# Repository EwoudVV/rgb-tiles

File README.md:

# RGB Tiles

modular 8 x 8 RGB LED tiles with an RP2040 on each board. connectors on all four edges let the tiles join into different shapes. all tiles face the same way

each tile is 99.5 mm square, with 64 WS2812C-V6 LEDs, 2 MB flash, USB-C and a four-layer PCB

open [rgb-tiles.kicad_pro](rgb-tiles.kicad_pro) in KiCad 10. [manufacturing/](manufacturing/) contains the Gerbers, drill files, BOM and purchase list. fabrication: four layers, 1.6 mm FR-4, JLC04161H-7628 stackup, 1 oz outer / 0.5 oz inner copper, lead-free HASL

power comes from a regulated 12 V supply at J7. USB is for data only. allow 1 A per tile and use a separate feed to each tile for full brightness. leave both edge power shunts out between separately fed sections. support the boards with a frame

[test firmware](firmware/README.md) displays dim red, green and blue stripes and reports received neighbor markers over USB serial

[Hack Club Half Life, week 4](https://halflife.hackclub.com/projects/c01og00redvbnb7qoo1i9yo8)

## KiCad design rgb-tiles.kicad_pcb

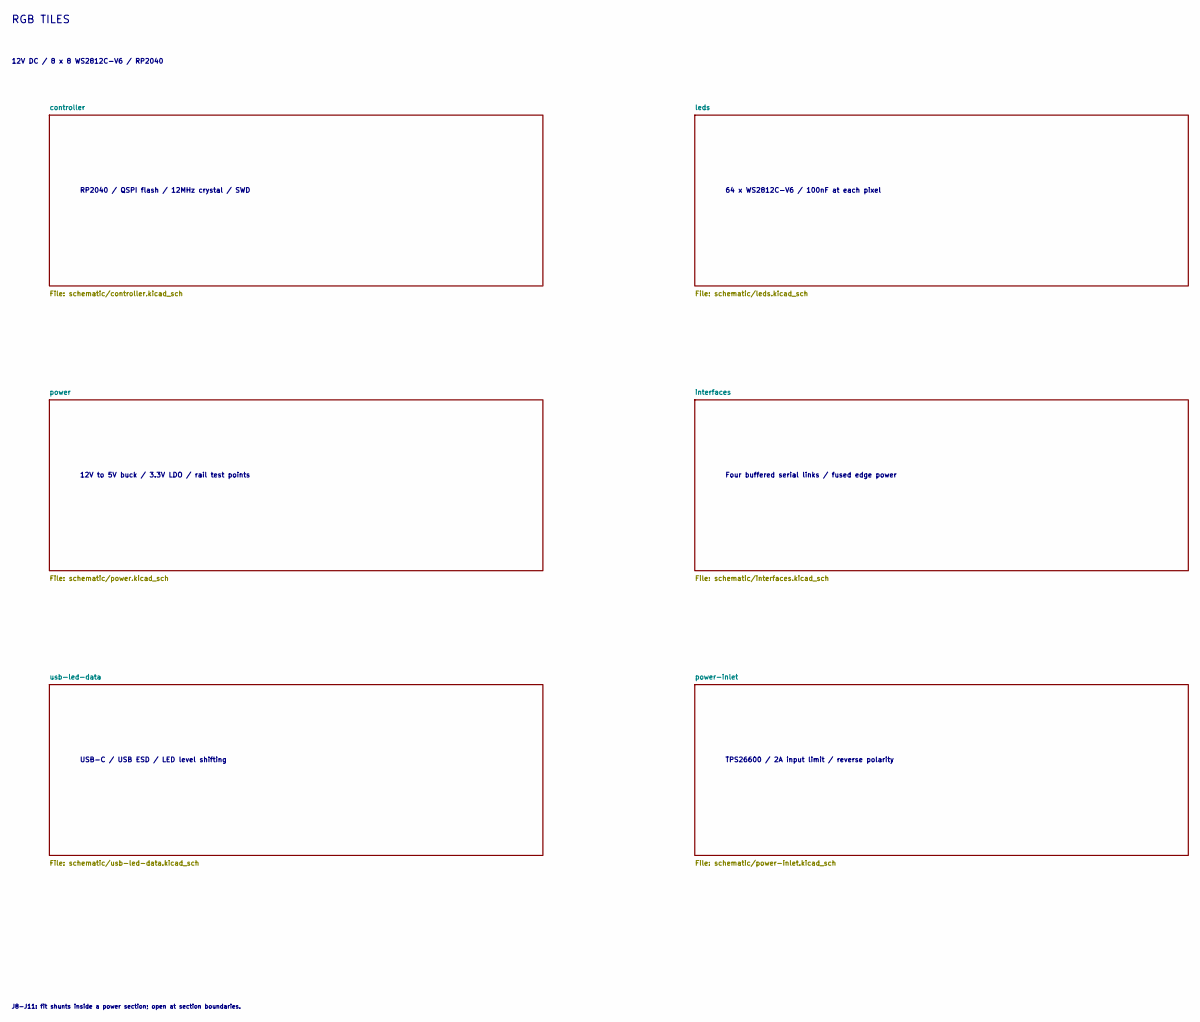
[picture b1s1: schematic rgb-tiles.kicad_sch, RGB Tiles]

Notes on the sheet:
RGB TILES
12V DC / 8 x 8 WS2812C-V6 / RP2040
J8-J11: fit shunts inside a power section; open at section boundaries.
RP2040 / QSPI flash / 12MHz crystal / SWD
64 x WS2812C-V6 / 100nF at each pixel
12V to 5V buck / 3.3V LDO / rail test points
Four buffered serial links / fused edge power
USB-C / USB ESD / LED level shifting
TPS26600 / 2A input limit / reverse polarity

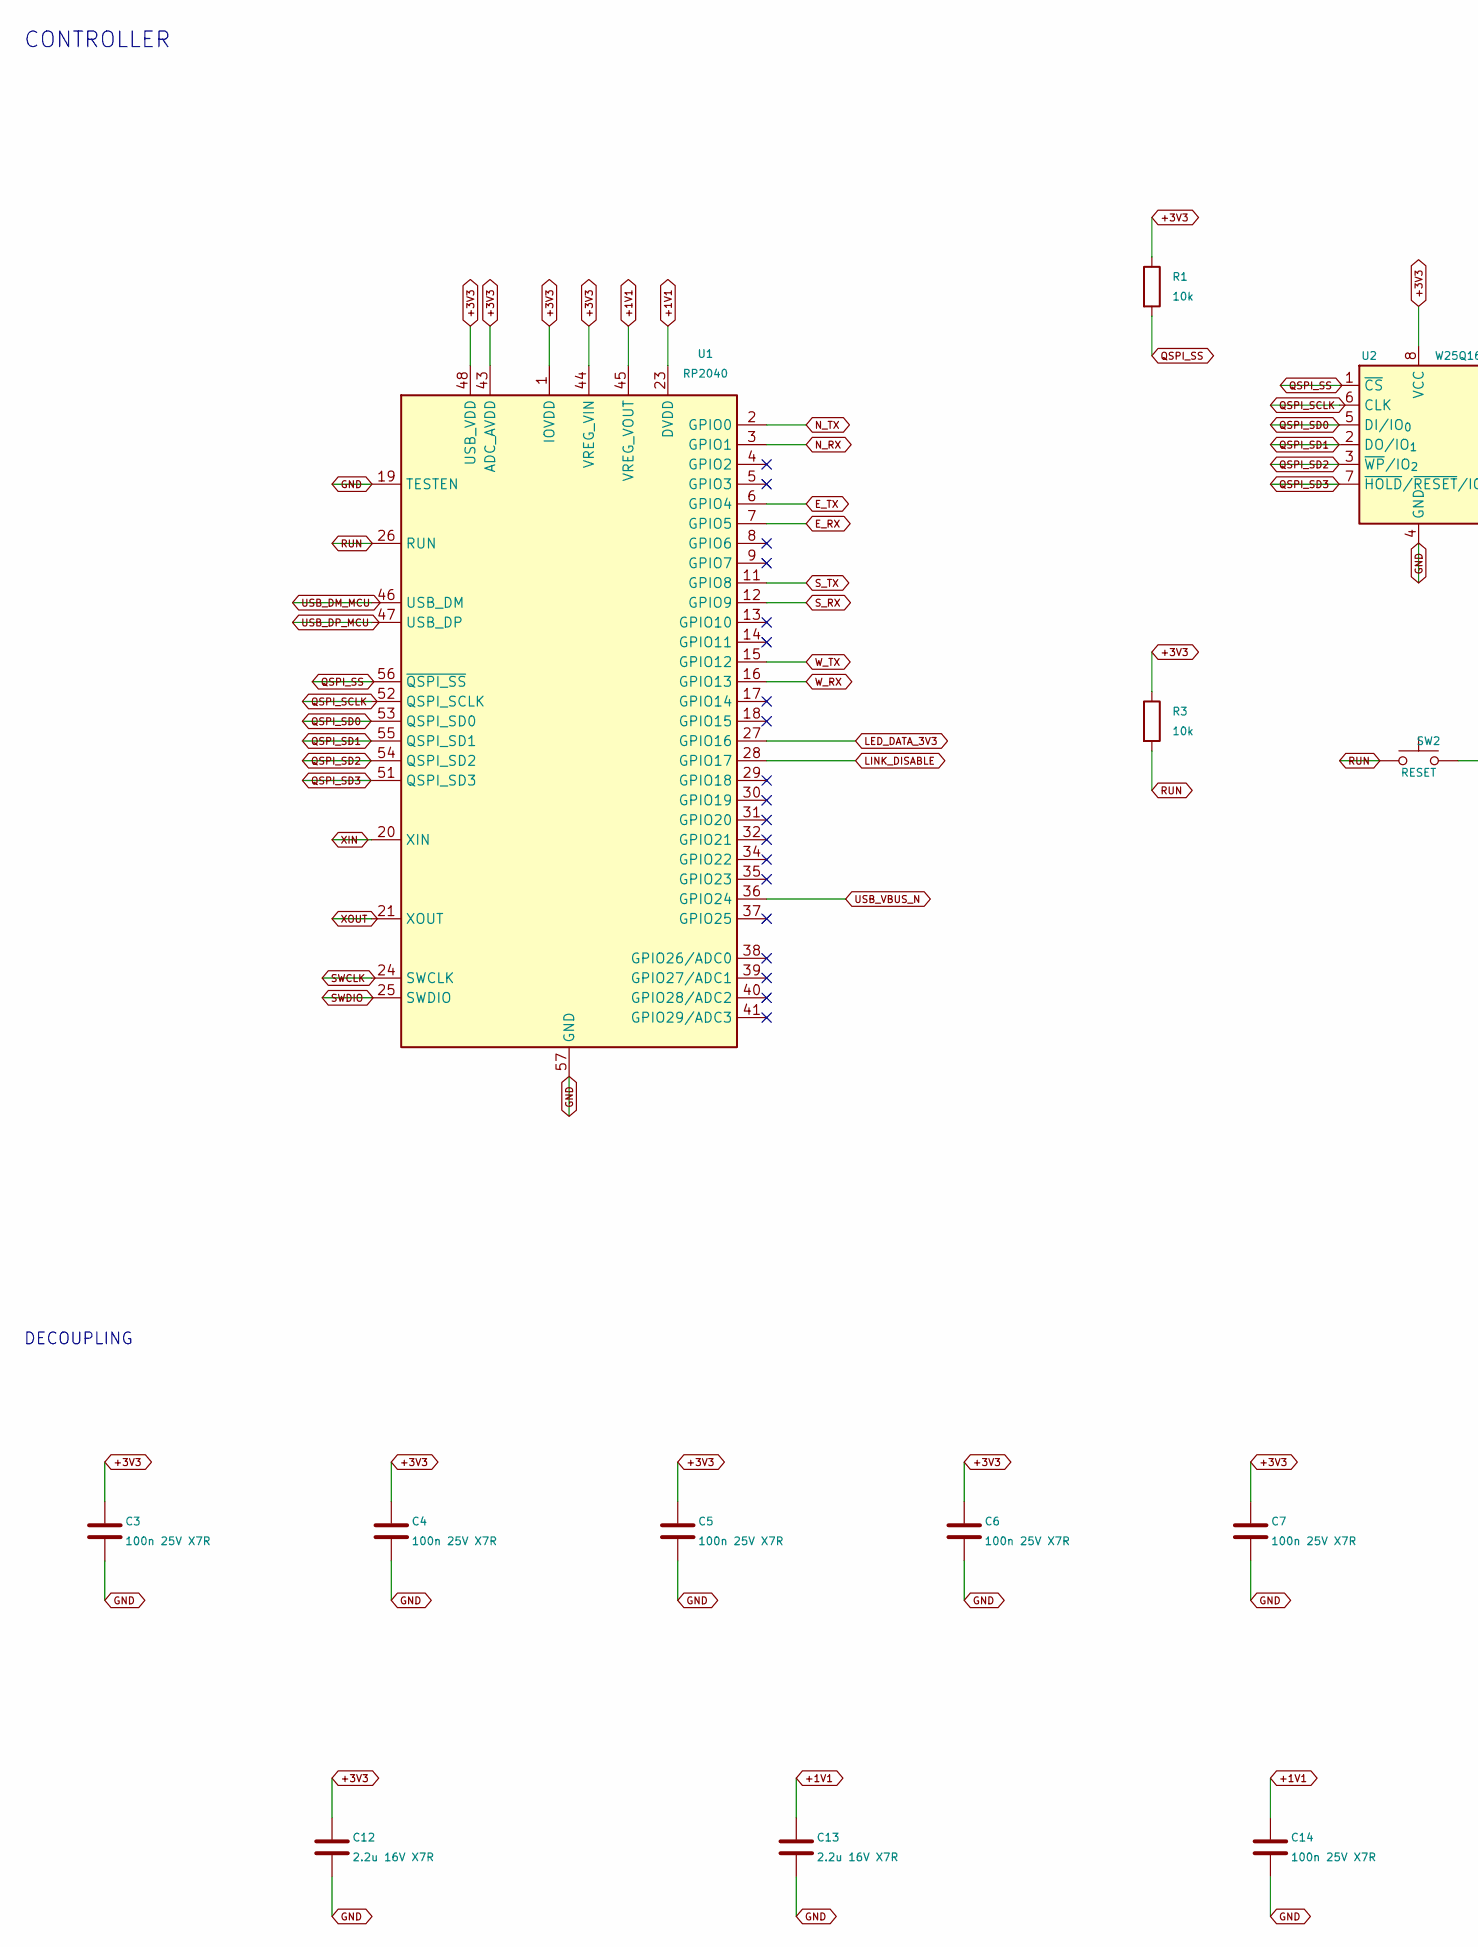
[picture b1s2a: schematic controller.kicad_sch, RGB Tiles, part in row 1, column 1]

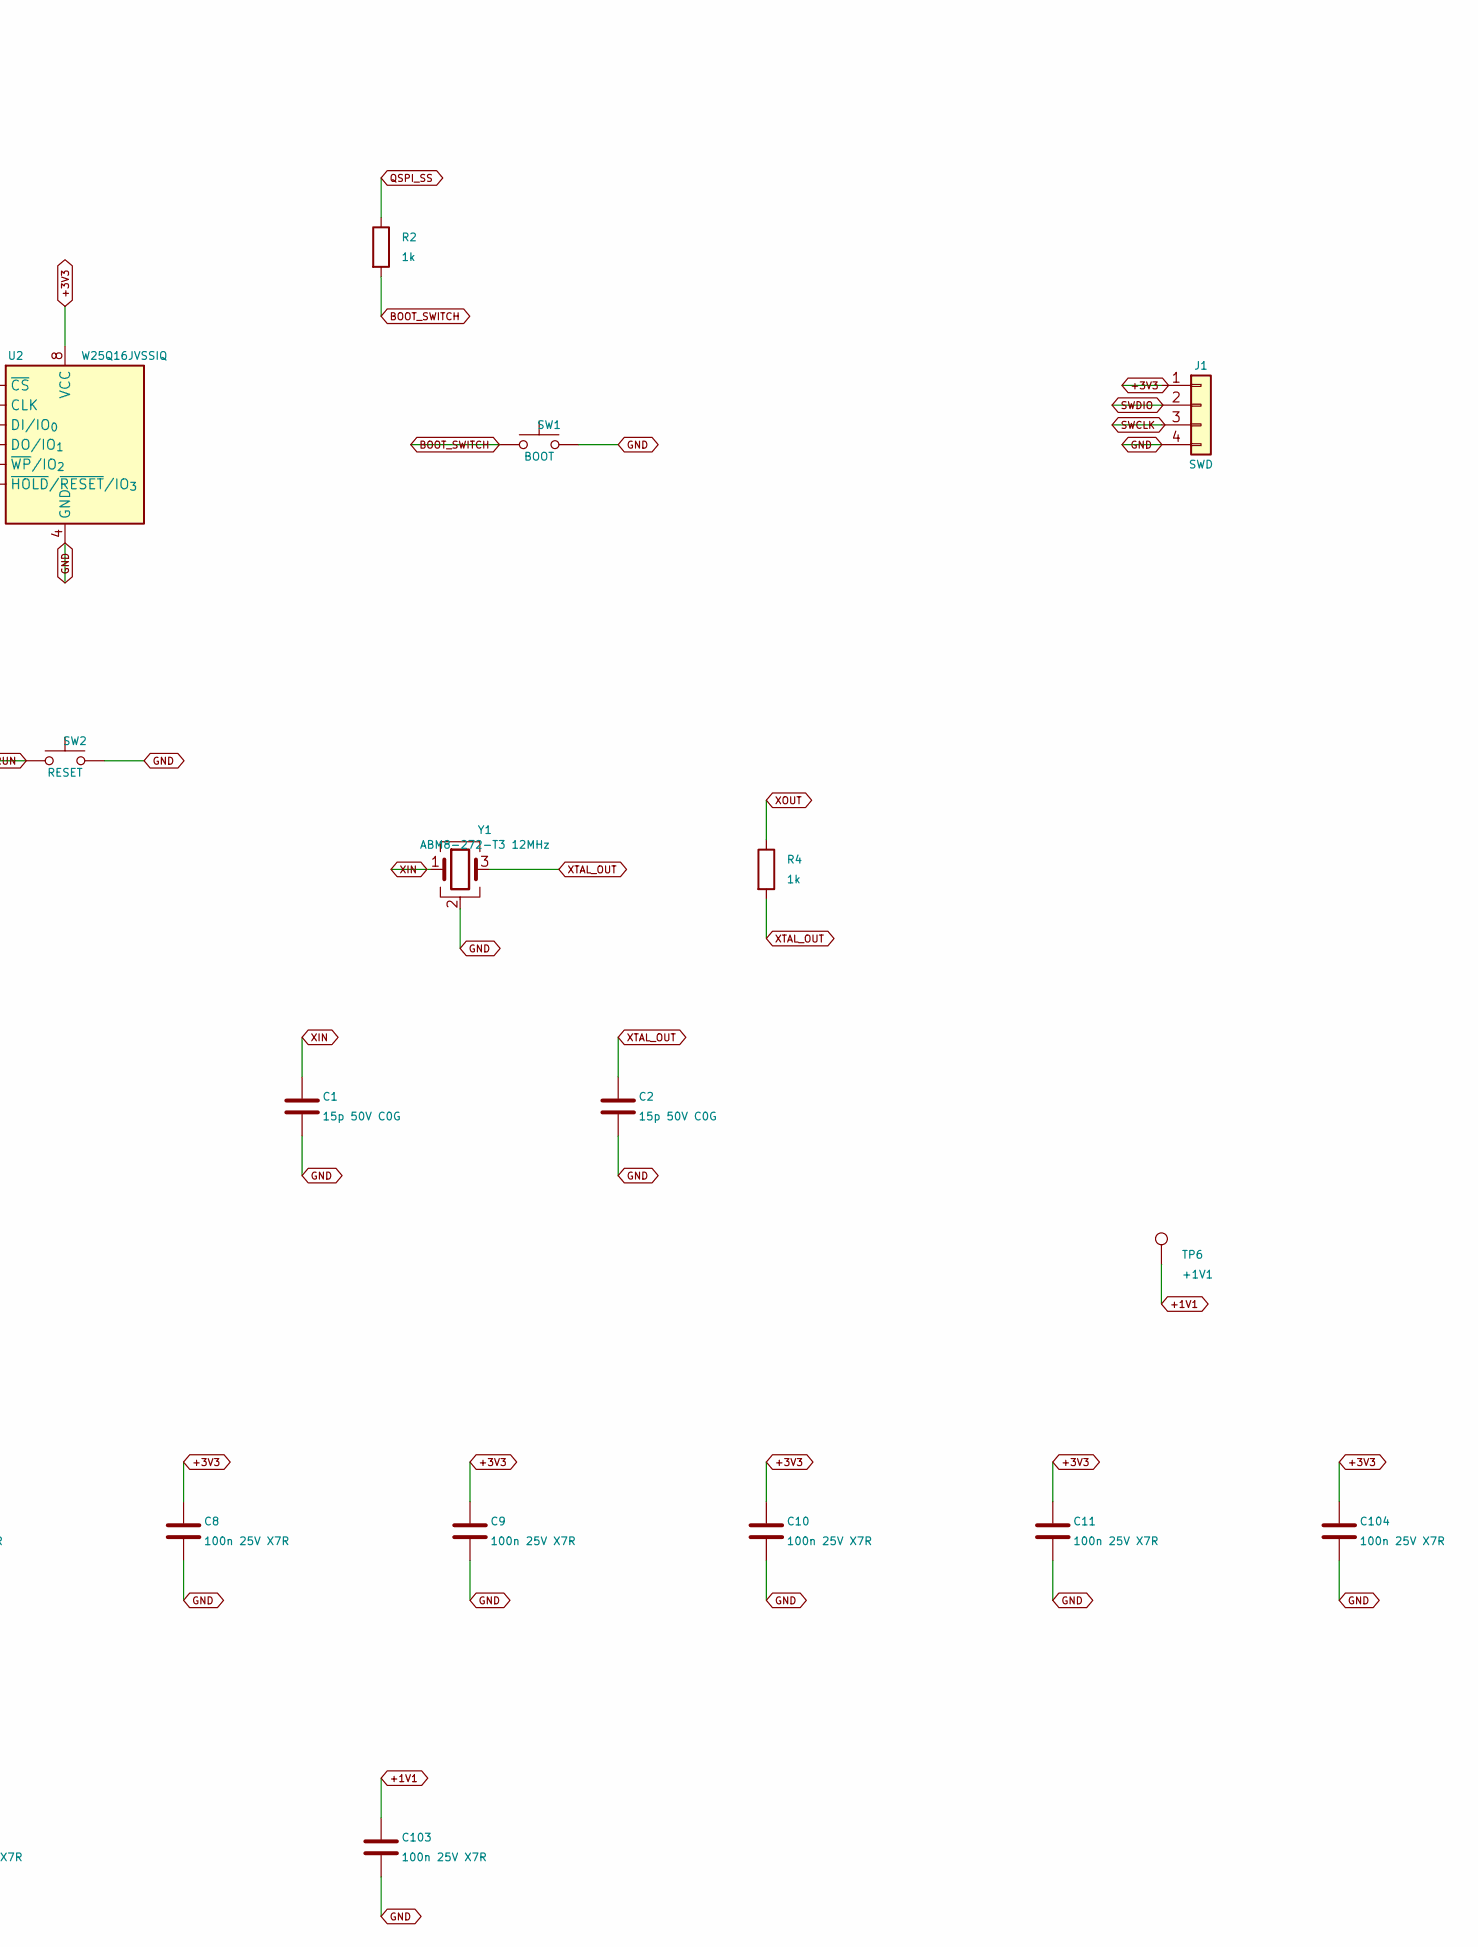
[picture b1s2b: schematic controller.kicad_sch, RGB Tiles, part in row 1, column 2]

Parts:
C1, C2: 15p 50V C0G; C_0603_1608Metric; MPN C0603C150J5GACTU
C3, C4, C5, C6, C7, C8, C9, C10, C11, C14, C103, C104: 100n 25V X7R; C_0603_1608Metric; MPN CL10B104KA8NNNC
C12, C13: 2.2u 16V X7R; C_0805_2012Metric; MPN C0805C225K4RACTU
J1: SWD; PinHeader_1x04_P2.54mm_Vertical; MPN TSW-104-07-T-S
R1, R3: 10k; R_0603_1608Metric; Tolerance 1%; MPN RC0603FR-0710KL
R2, R4: 1k; R_0603_1608Metric; Tolerance 1%; MPN RC0603FR-071KL
SW1: BOOT; SW_SPST_TL3342; MPN TL3342F160QG
SW2: RESET; SW_SPST_TL3342; MPN TL3342F160QG
TP6: +1V1; TestPoint_Pad_D1.5mm
U1: RP2040; QFN-56-1EP_7x7mm_P0.4mm_EP3.2x3.2mm; MPN RP2040
U2: W25Q16JVSSIQ; SOIC-8_5.3x5.3mm_P1.27mm; MPN W25Q16JVSSIM
Y1: ABM8-272-T3 12MHz; Crystal_SMD_3225-4Pin_3.2x2.5mm; MPN ABM8-272-T3

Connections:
+1V1: C13.1, C14.1, C103.1, TP6.1, U1.23 (DVDD), U1.45 (VREG_VOUT), U1.50 (DVDD)
+3V3: C3.1, C4.1, C5.1, C6.1, C7.1, C8.1, C9.1, C10.1, C11.1, C12.1, C104.1, J1.1, R1.1, R3.1, U1.1 (IOVDD), U1.10 (IOVDD), U1.22 (IOVDD), U1.33 (IOVDD), U1.42 (IOVDD), U1.43 (ADC_AVDD), U1.44 (VREG_VIN), U1.48 (USB_VDD), U1.49 (IOVDD), U2.8 (VCC); also elsewhere on the board
BOOT_SWITCH: R2.2, SW1.1
E_RX: U1.7 (GPIO5); also elsewhere on the board
E_TX: U1.6 (GPIO4); also elsewhere on the board
GND: C1.2, C2.2, C3.2, C4.2, C5.2, C6.2, C7.2, C8.2, C9.2, C10.2, C11.2, C12.2, C13.2, C14.2, C103.2, C104.2, J1.4, SW1.2, SW2.2, U1.19 (TESTEN), U1.57 (GND), U2.4 (GND), Y1.2 (G), Y1.4 (G); also elsewhere on the board
LED_DATA_3V3: U1.27 (GPIO16); also elsewhere on the board
LINK_DISABLE: U1.28 (GPIO17); also elsewhere on the board
N_RX: U1.3 (GPIO1); also elsewhere on the board
N_TX: U1.2 (GPIO0); also elsewhere on the board
QSPI_SCLK: U1.52 (QSPI_SCLK), U2.6 (CLK)
QSPI_SD0: U1.53 (QSPI_SD0), U2.5 (DI/IO_{0})
QSPI_SD1: U1.55 (QSPI_SD1), U2.2 (DO/IO_{1})
QSPI_SD2: U1.54 (QSPI_SD2), U2.3 (~WP/IO_{2})
QSPI_SD3: U1.51 (QSPI_SD3), U2.7 (~HOLD/~RESET/IO_{3})
QSPI_SS: R1.2, R2.1, U1.56 (~QSPI_SS), U2.1 (~CS)
RUN: R3.2, SW2.1, U1.26 (RUN)
SWCLK: J1.3, U1.24 (SWCLK)
SWDIO: J1.2, U1.25 (SWDIO)
S_RX: U1.12 (GPIO9); also elsewhere on the board
S_TX: U1.11 (GPIO8); also elsewhere on the board
USB_DM_MCU: U1.46 (USB_DM); also elsewhere on the board
USB_DP_MCU: U1.47 (USB_DP); also elsewhere on the board
USB_VBUS_N: U1.36 (GPIO24); also elsewhere on the board
W_RX: U1.16 (GPIO13); also elsewhere on the board
W_TX: U1.15 (GPIO12); also elsewhere on the board
XIN: C1.1, U1.20 (XIN), Y1.1
XOUT: R4.1, U1.21 (XOUT)
XTAL_OUT: C2.1, R4.2, Y1.3

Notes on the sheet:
CONTROLLER
DECOUPLING
